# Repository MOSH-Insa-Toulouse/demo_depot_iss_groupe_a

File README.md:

# demo_depot_iss_groupe_a
Ceci est une demo

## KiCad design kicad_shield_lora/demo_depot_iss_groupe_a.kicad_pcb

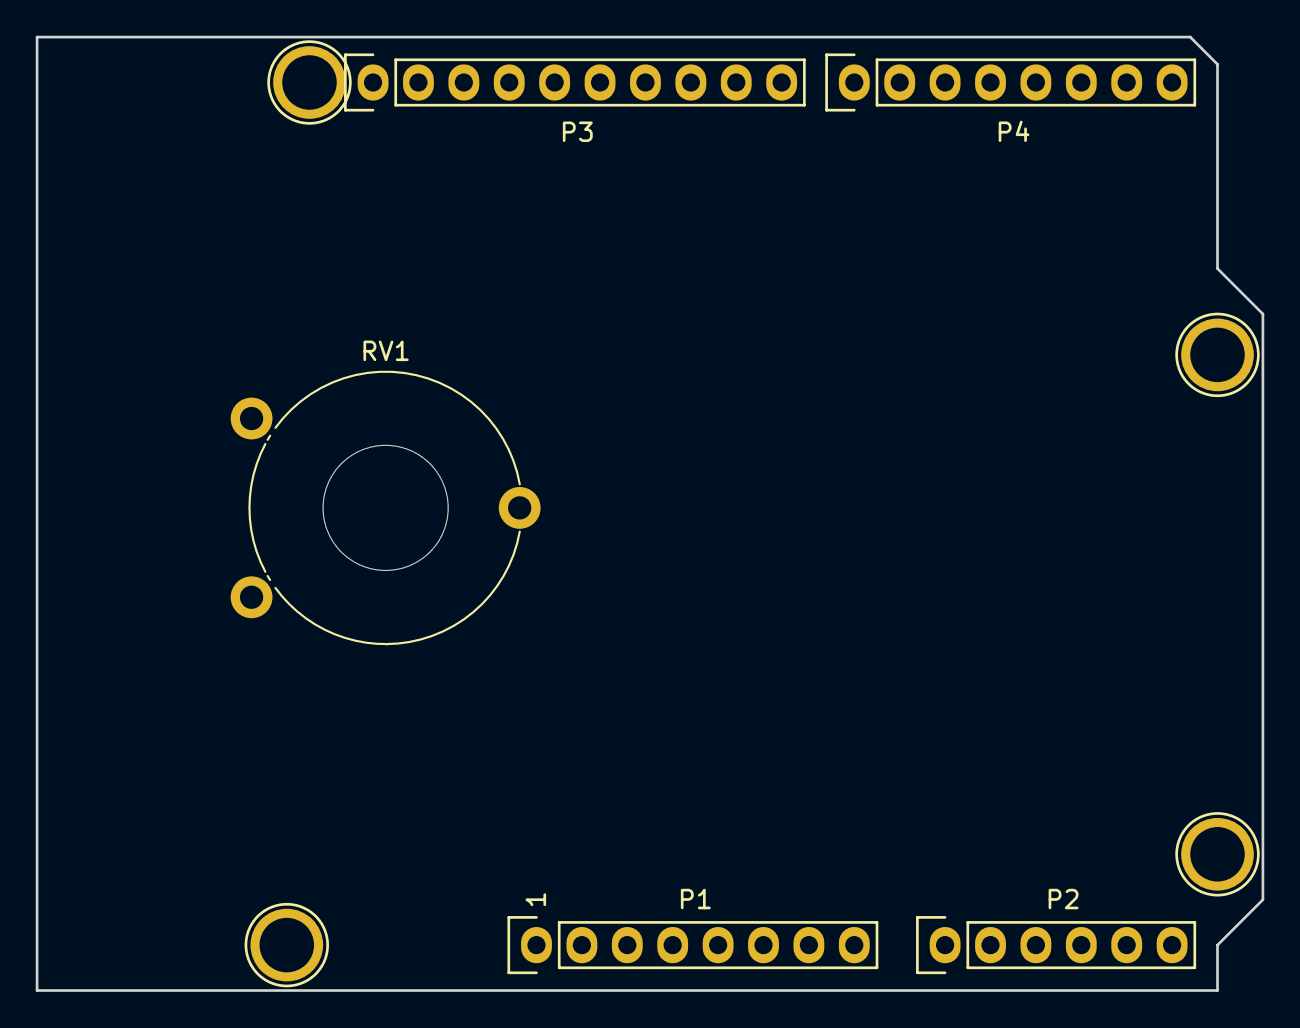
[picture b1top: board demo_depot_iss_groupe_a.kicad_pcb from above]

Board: 2 copper layers, 68.6 x 53.3 mm, 9 parts (0 on the bottom side), 5 nets, no tracks yet.

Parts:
P1: Power; Socket_Strip_Arduino_1x08
P2: Analog; Socket_Strip_Arduino_1x06
P3: Digital; Socket_Strip_Arduino_1x10
P4: Digital; Socket_Strip_Arduino_1x08
P5, P6, P7, P8: CONN_01X01; Arduino_1pin
RV1: R_POT; Potentiometer_Piher_PT-15-V15_Vertical_Hole

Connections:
+5V: P1.5, RV1.1
/A0: P2.1, RV1.2
/A4(SDA): P2.5, P3.2
/A5(SCL): P2.6, P3.1
GND: P1.6, P1.7, P3.4, RV1.3

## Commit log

2018-10-04 Demmarrage du projet de shield
